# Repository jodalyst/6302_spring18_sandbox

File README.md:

# 6302_spring18_sandbox
Holding and Testing Location for 6.302 S18 Development Work

## Installation Instructions

Currently the browser interface for this setup is served using Flask for local CORS suppression.  For deployment on a local computer you need to do:

```
pip install flask flask-cors
```

This has only been tested on Python3, so make sure you are installing it for Python3.

On the microcontroller side:

* First have the ESP32 Arduino core installed properly.
* Add `ESP32-Websocket` library to your Arduino libraries folder
* Inside the `examples` folder there is the `ESP32_Streaming` example.  That needs to be put onto the ESP32.  Before you do that, make sure you enter the SSID and password for the network you are using your computer on at the top.

When the code is flashed to the ESP32, open up the serial monitor. It will print the IP address it was assigned by your local router.   If you missed it/opened the Serial Monitor up too late, just reset the ESP32 (no danger like with Teensy)

Before or after you upload, feel free to start the minimal server:

```
python3 base.py
```

Then go to `localhost:5000`

A plot of two things (mouse x/y for testing purposes) and what will be data from the ESP is present. No data will be plotting from the ESP32 since you need to establish connection.  To do that, enter the IP address of your ESP32 in the field at top...so if it is 192.168.0.105 enter:

```
192.168.0.105
```

for example...no spaces and must include the `.`.  

Data should immediately start streaming (this was designed using a three axis analog-out accelerometer on it, but even without, random values will be getting plotted)

*Note the ESP32-Websocket Library is a lightly-modified version of the ESP8266 Websocket Library (found <a href="https://github.com/morrissinger/ESP8266-Websocket" target="_blank">here</a>)

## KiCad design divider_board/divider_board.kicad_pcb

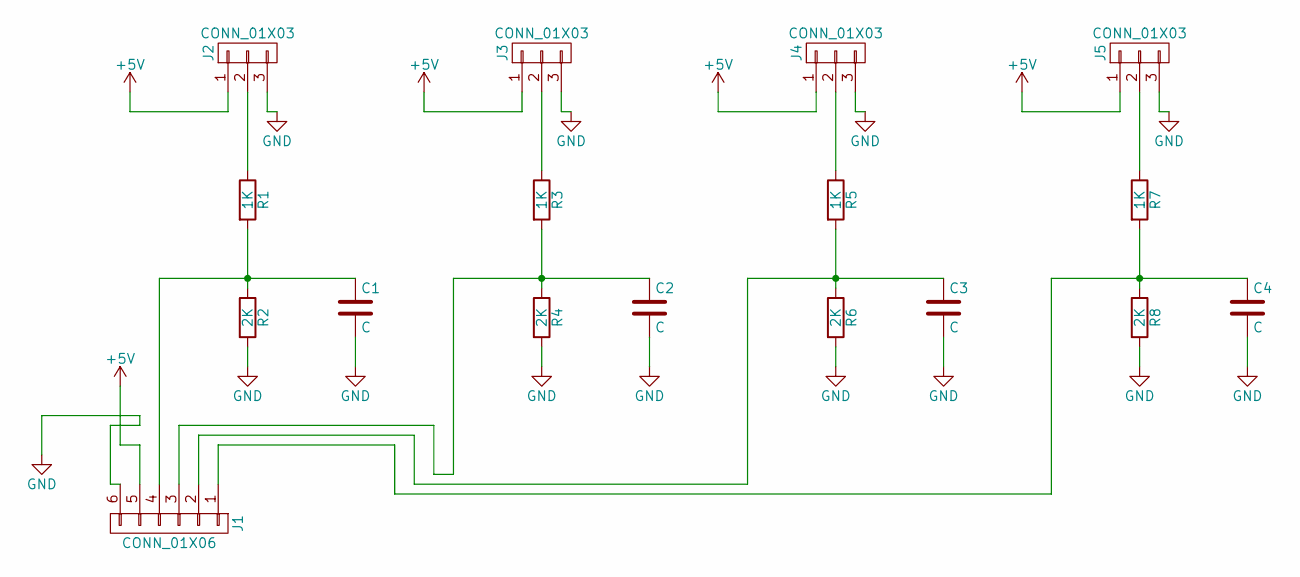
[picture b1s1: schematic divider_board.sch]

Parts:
C1, C2, C3, C4: C; C_0805
J1: CONN_01X06; 1X06
J2, J3, J4, J5: CONN_01X03; 1X03
R1, R3, R5, R7: 1K; R_0805
R2, R4, R6, R8: 2K; R_0805

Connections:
+5V: J1.5, J2.1, J3.1, J4.1, J5.1
GND: C1.2, C2.2, C3.2, C4.2, J1.6, J2.3, J3.3, J4.3, J5.3, R2.2, R4.2, R6.2, R8.2
unnamed: C1.1, J1.4, R1.2, R2.1
unnamed: C2.1, J1.3, R3.2, R4.1
unnamed: C3.1, J1.2, R5.2, R6.1
unnamed: C4.1, J1.1, R7.2, R8.1
unnamed: J2.2, R1.1
unnamed: J3.2, R3.1
unnamed: J4.2, R5.1
unnamed: J5.2, R7.1

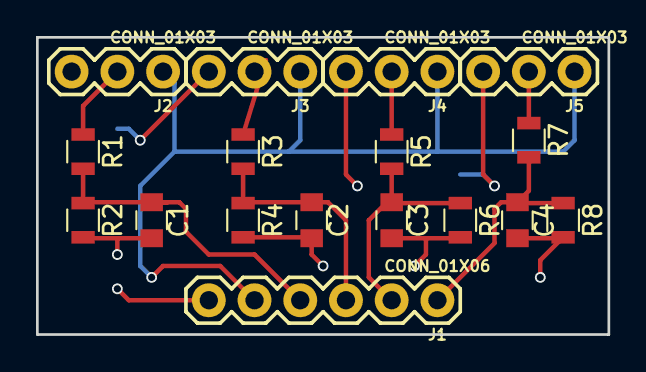
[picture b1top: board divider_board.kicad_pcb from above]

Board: 2 copper layers, 31.8 x 16.5 mm, 17 parts (0 on the bottom side), 10 nets.

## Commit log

2017-12-20 adding in divider board version 1
